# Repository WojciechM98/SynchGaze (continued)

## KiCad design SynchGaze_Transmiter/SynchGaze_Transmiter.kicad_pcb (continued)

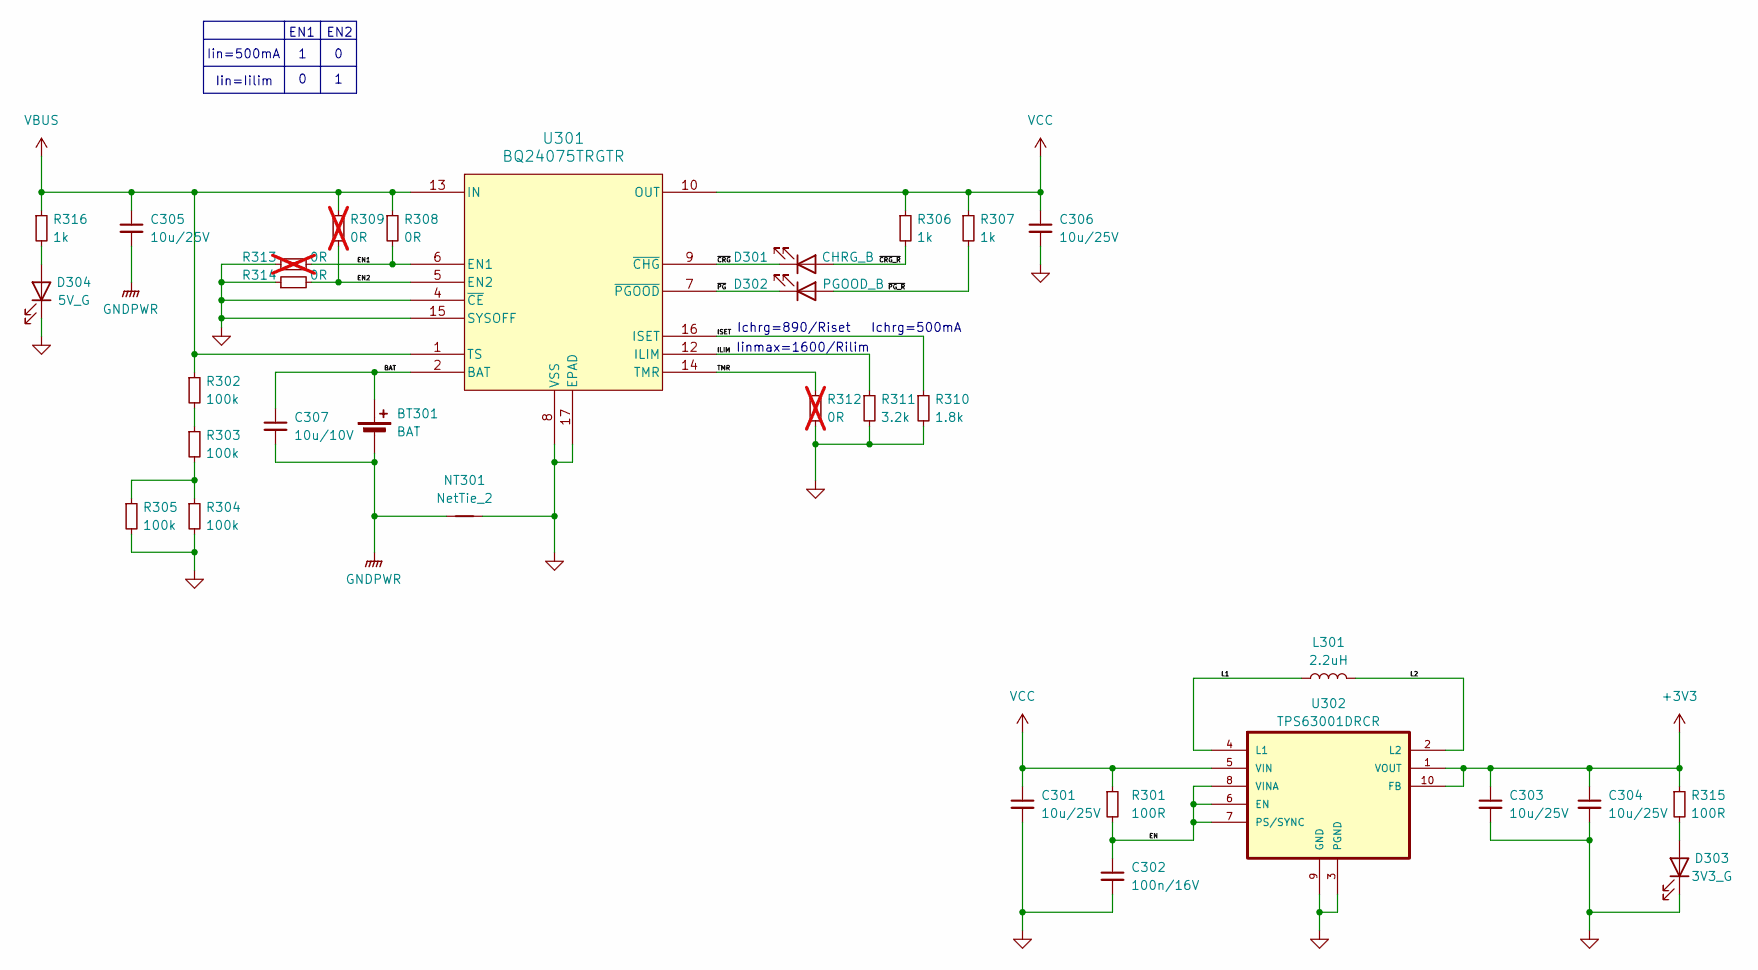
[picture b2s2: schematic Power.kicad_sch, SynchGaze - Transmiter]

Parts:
BT301: BAT; SM02B-SRSS-TB_LF__SN_; Manufacturer Part Number ACCU-LP542439/CL
C301, C303, C304, C305, C306: 10u/25V; C_1206_3216Metric; Manufacturer Part Number CL31B106KAHNFNE
C302: 100n/16V; C_0402_1005Metric; Manufacturer Part Number CL05B104JO5NNNC
C307: 10u/10V; C_0402_1005Metric; Manufacturer Part Number GRM155R61A106ME11J
D301: CHRG_B; LED_0603_1608Metric; Manufacturer Part Number 150060BS55040
D302: PGOOD_B; LED_0603_1608Metric; Manufacturer Part Number 150060BS55040
D303: 3V3_G; LED_0603_1608Metric; Manufacturer Part Number 150060GS55040
D304: 5V_G; LED_0603_1608Metric; Manufacturer Part Number 150060GS55040
L301: 2.2uH; L_Abracon_ASPI-3012S; Manufacturer Part Number NRH3012T2R2MNV
NT301: NetTie_2; NetTie-2_SMD_0.4mm
R301, R315: 100R; R_0402_1005Metric; Manufacturer Part Number RC0402JR-07100RP
R302, R303, R304, R305: 100k; R_0402_1005Metric; Manufacturer Part Number WR04X104 JTL
R306, R307, R316: 1k; R_0402_1005Metric; Manufacturer Part Number RT0402FRE071KL
R308, R314: 0R; R_0402_1005Metric; Manufacturer Part Number RC0402JR-070RP
R309, R312, R313: 0R; R_0402_1005Metric; Manufacturer Part Number RC0402JR-070RP; not fitted
R310: 1.8k; R_0402_1005Metric; Manufacturer Part Number RT0402FRE071K8L
R311: 3.2k; R_0402_1005Metric; Manufacturer Part Number RT0402DRE073K2L
U301: BQ24075TRGTR; Manufacturer Part Number BQ24075TRGTR
U302: TPS63001DRCR; VREG_V62_16624-01YE_TPS63001DRCR; Manufacturer Part Number TPS63001DRCR

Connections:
+3V3: C303.1, C304.1, R315.1, U302.1 (VOUT), U302.10 (FB); also elsewhere on the board
/Power/BAT: BT301.1 (+), C307.1, U301.2 (BAT), U301.3 (BAT)
/Power/EN: C302.1, R301.2, U302.6 (EN), U302.7 (PS/SYNC), U302.8 (VINA)
/Power/EN1: R308.2, R313.2, U301.6 (EN1)
/Power/EN2: R309.2, R314.2, U301.5 (EN2)
/Power/ILIM: R311.1, U301.12 (ILIM)
/Power/ISET: R310.1, U301.16 (ISET)
/Power/L1: L301.1, U302.4 (L1)
/Power/L2: L301.2, U302.2 (L2)
/Power/TMR: R312.1, U301.14 (TMR)
/Power/~CRG_R: D301.2 (A), R306.2
/Power/~CRG: D301.1 (K), U301.9 (~CHG)
/Power/~PG_R: D302.2 (A), R307.2
/Power/~PG: D302.1 (K), U301.7 (~PGOOD)
GND: C301.2, C302.2, C303.2, C304.2, C306.2, D303.1 (K), D304.1 (K), NT301.2, R304.2, R305.2, R310.2, R311.2, R312.2, R313.1, R314.1, U301.4 (~CE), U301.8 (VSS), U301.15 (SYSOFF), U301.17 (EPAD), U302.3 (PGND), U302.9 (GND), U302.11 (POWER_PAD); also elsewhere on the board
GNDPWR: BT301.2 (-), C305.2, C307.2, NT301.1
unnamed: D303.2 (A), R315.2
unnamed: D304.2 (A), R316.2
unnamed: R302.2, R303.1
unnamed: R303.2, R304.1, R305.1
VBUS: C305.1, R302.1, R308.1, R309.1, R316.1, U301.1 (TS), U301.13 (IN); also elsewhere on the board
VCC: C301.1, C306.1, R301.1, R306.1, R307.1, U301.10 (OUT), U301.11 (OUT), U302.5 (VIN)

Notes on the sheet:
Iin=500mA
EN1
EN2
Iin=Iilim
Iinmax=1600/Rilim
Ichrg=500mA
Ichrg=890/Riset

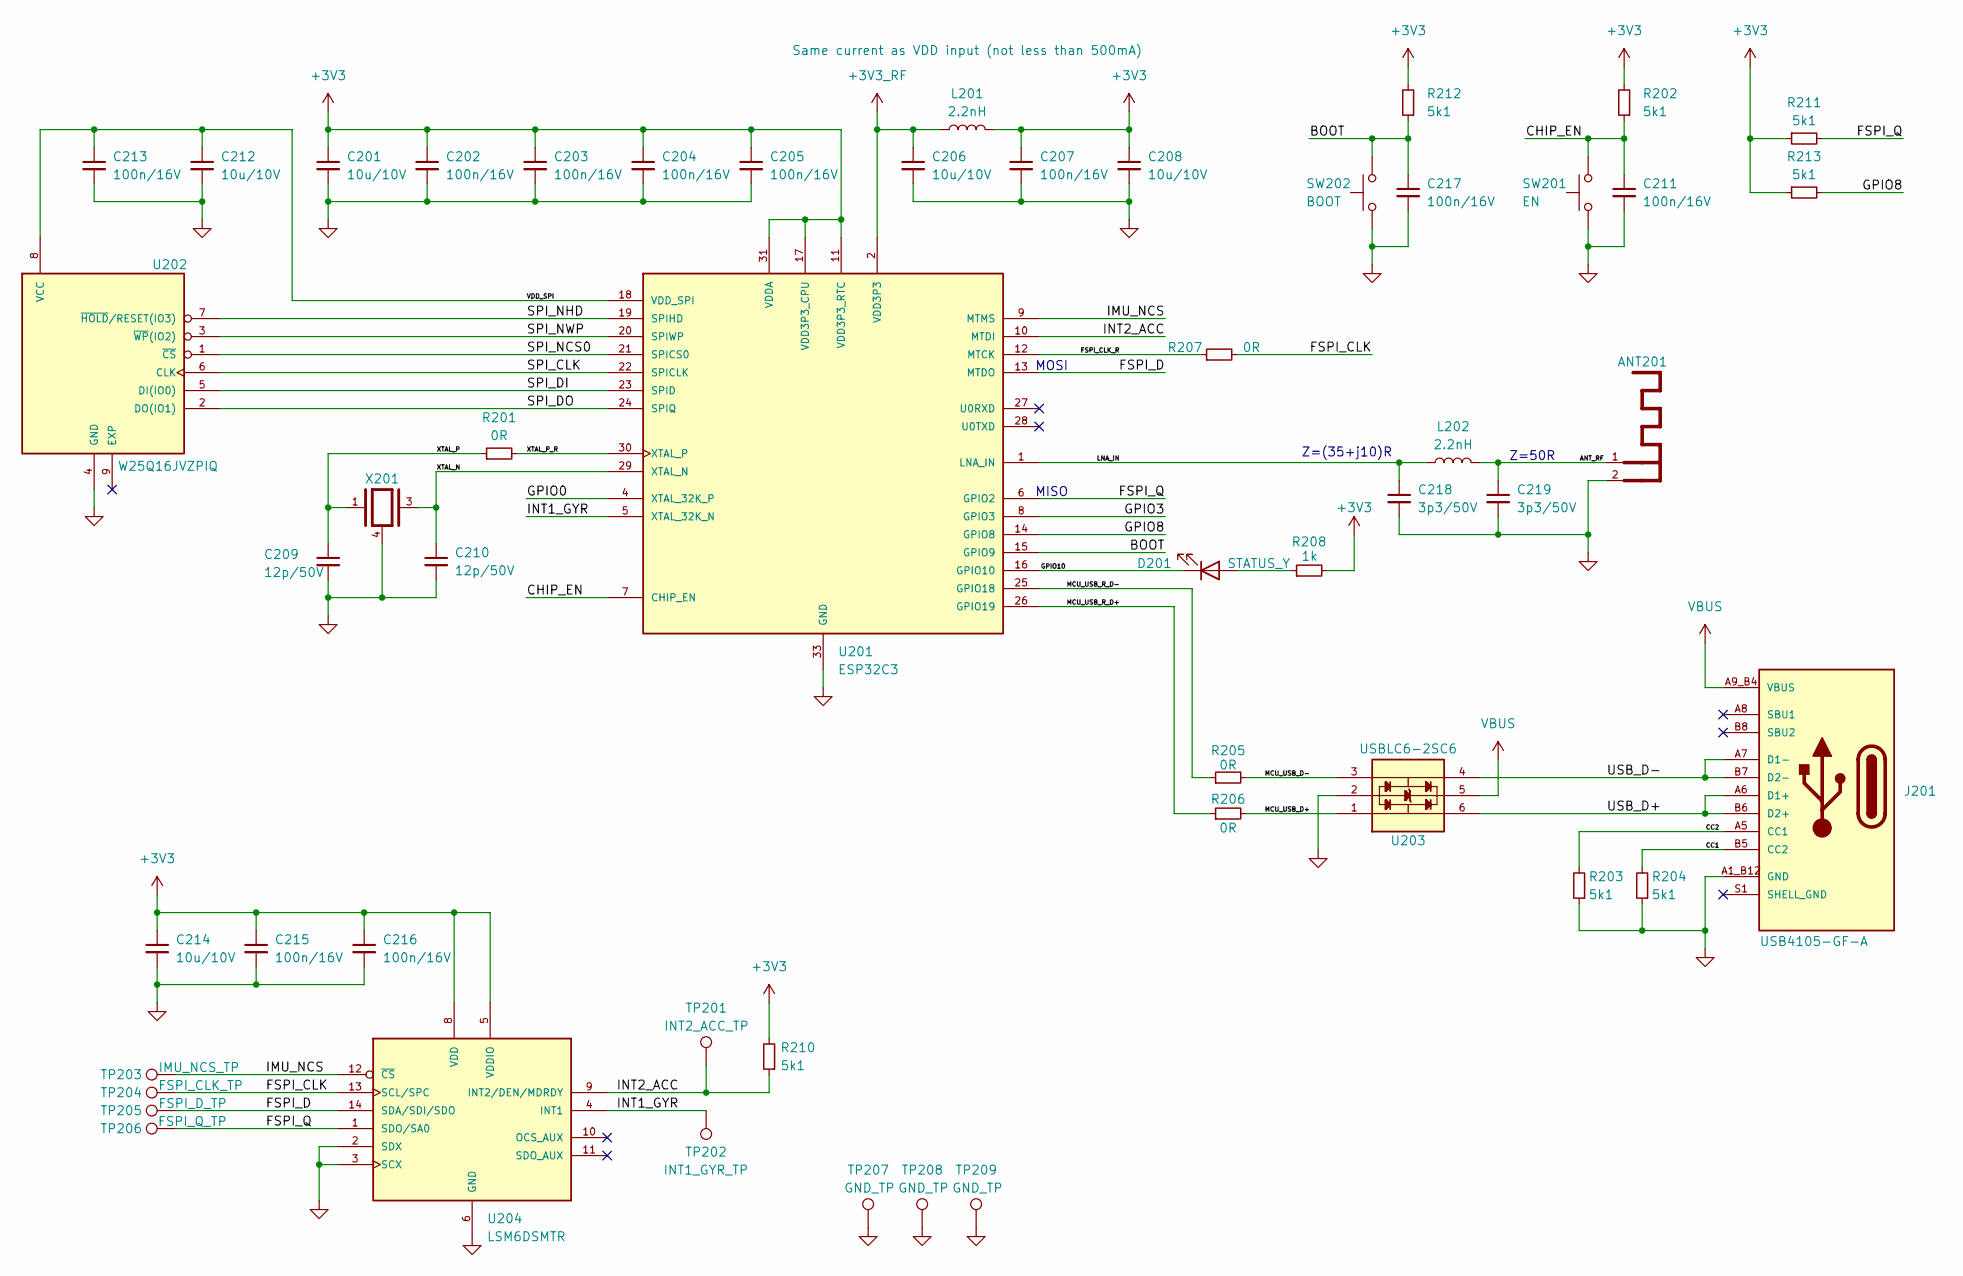
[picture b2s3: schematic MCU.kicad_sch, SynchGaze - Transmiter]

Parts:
ANT201: Ant_2_4ghz_50ohm
C201, C206, C208, C212, C214: 10u/10V; C_0402_1005Metric; Manufacturer Part Number GRM155R61A106ME11J
C202, C203, C204, C205, C207, C211, C213, C215, C216, C217: 100n/16V; C_0402_1005Metric; Manufacturer Part Number CL05B104JO5NNNC
C209, C210: 12p/50V; C_0402_1005Metric; Manufacturer Part Number GRM1555C1H120JA01D
C218, C219: 3p3/50V; C_0402_1005Metric; Manufacturer Part Number 0402N3R3D500CT
D201: STATUS_Y; LED_0603_1608Metric; Manufacturer Part Number 150060YS55040
J201: USB4105-GF-A; GCT_USB4105-GF-A; PARTREV 3
L201, L202: 2.2nH; L_0402_1005Metric; Manufacturer Part Number LQG15HN2N2S02D
R201, R205, R206, R207: 0R; R_0402_1005Metric; Manufacturer Part Number RC0402JR-070RP
R202, R203, R204, R210, R211, R212, R213: 5k1; R_0402_1005Metric; Manufacturer Part Number RT0402FRE075K1L
R208: 1k; R_0402_1005Metric; Manufacturer Part Number RT0402FRE071KL
SW201: EN; SW4_PTS815 SJM 250 SMTR LFS_CNK; Manufacturer Part Number RKB2SJM250SMTR LFS
SW202: BOOT; SW4_PTS815 SJM 250 SMTR LFS_CNK; Manufacturer Part Number RKB2SJM250SMTR LFS
TP201: INT2_ACC_TP; test_point_SMD_0.5mm
TP202: INT1_GYR_TP; test_point_SMD_0.5mm
TP203: IMU_NCS_TP; test_point_SMD_0.5mm
TP204: FSPI_CLK_TP; test_point_SMD_0.5mm
TP205: FSPI_D_TP; test_point_SMD_0.5mm
TP206: FSPI_Q_TP; test_point_SMD_0.5mm
TP207, TP208, TP209: GND_TP; test_point_THT 0.7mm
U201: ESP32C3; QFN32_5X5MM_ESP32C3; Manufacturer Part Number ESP32-C3
U202: W25Q16JVZPIQ; SON127P500X600X80-9N; Manufacturer Part Number W25Q16JVZPIQ
U203: USBLC6-2SC6; SOT95P280X145-6N; Manufacturer Part Number USBLC6-2SC6
U204: LSM6DSMTR; PQFN50P300X250X86-14N_LSM6DSMTR; PARTREV Rev 7
X201: XRCGB40M000F4M02R0; OSC_XRCGB40M000F4M02R0; PARTREV N/A

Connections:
+3V3: C201.1, C202.1, C203.1, C204.1, C205.1, C207.1, C208.1, C214.1, C215.1, C216.1, L201.2, R202.2, R208.2, R210.2, R211.1, R212.2, R213.1, U201.11 (VDD3P3_RTC), U201.17 (VDD3P3_CPU), U201.31 (VDDA), U201.32 (VDDA), U204.5 (VDDIO), U204.8 (VDD); also elsewhere on the board
+3V3_RF: C206.1, L201.1, U201.2 (VDD3P3), U201.3 (VDD3P3)
/MCU/ANT_RF: ANT201.1, C219.1, L202.2
/MCU/BOOT: C217.1, R212.1, SW202.2, U201.15 (GPIO9)
/MCU/CC1: J201.B5 (CC2), R204.2
/MCU/CC2: J201.A5 (CC1), R203.2
/MCU/CHIP_EN: C211.1, R202.1, SW201.2, U201.7 (CHIP_EN)
/MCU/FSPI_CLK: R207.2, TP204.1, U204.13 (SCL/SPC)
/MCU/FSPI_CLK_R: R207.1, U201.12 (MTCK)
/MCU/FSPI_D: TP205.1, U201.13 (MTDO), U204.14 (SDA/SDI/SDO)
/MCU/FSPI_Q: R211.2, TP206.1, U201.6 (GPIO2), U204.1 (SDO/SA0)
/MCU/GPIO0: U201.4 (XTAL_32K_P)
/MCU/GPIO3: U201.8 (GPIO3)
/MCU/GPIO8: R213.2, U201.14 (GPIO8)
/MCU/GPIO10: D201.1 (K), U201.16 (GPIO10)
/MCU/IMU_NCS: TP203.1, U201.9 (MTMS), U204.12 (~CS)
/MCU/INT1_GYR: TP202.1, U201.5 (XTAL_32K_N), U204.4 (INT1)
/MCU/INT2_ACC: R210.1, TP201.1, U201.10 (MTDI), U204.9 (INT2/DEN/MDRDY)
/MCU/LNA_IN: C218.1, L202.1, U201.1 (LNA_IN)
/MCU/MCU_USB_D+: R206.2, U203.1
/MCU/MCU_USB_D-: R205.2, U203.3
/MCU/MCU_USB_R_D+: R206.1, U201.26 (GPIO19)
/MCU/MCU_USB_R_D-: R205.1, U201.25 (GPIO18)
/MCU/SPI_CLK: U201.22 (SPICLK), U202.6 (CLK)
/MCU/SPI_DI: U201.23 (SPID), U202.5 (DI(IO0))
/MCU/SPI_DO: U201.24 (SPIQ), U202.2 (DO(IO1))
/MCU/SPI_NCS0: U201.21 (SPICS0), U202.1 (~CS)
/MCU/SPI_NHD: U201.19 (SPIHD), U202.7 (~HOLD/RESET(IO3))
/MCU/SPI_NWP: U201.20 (SPIWP), U202.3 (~WP(IO2))
/MCU/USB_D+: J201.A6 (D1+), J201.B6 (D2+), U203.6
/MCU/USB_D-: J201.A7 (D1-), J201.B7 (D2-), U203.4
/MCU/VDD_SPI: C212.1, C213.1, U201.18 (VDD_SPI), U202.8 (VCC)
/MCU/XTAL_N: C210.1, U201.29 (XTAL_N), X201.3
/MCU/XTAL_P: C209.1, R201.1, X201.1
/MCU/XTAL_P_R: R201.2, U201.30 (XTAL_P)
GND: ANT201.2, C201.2, C202.2, C203.2, C204.2, C205.2, C206.2, C207.2, C208.2, C209.2, C210.2, C211.2, C212.2, C213.2, C214.2, C215.2, C216.2, C217.2, C218.2, C219.2, J201.A1_B12 (GND), J201.A12_B1 (GND), R203.1, R204.1, SW201.1, SW202.1, TP207.1, TP208.1, TP209.1, U201.33 (GND), U202.4 (GND), U203.2, U204.2 (SDX), U204.3 (SCX), U204.6 (GND), U204.7 (GND), X201.2, X201.4; also elsewhere on the board
unnamed: D201.2 (A), R208.1
VBUS: J201.A4_B9 (VBUS), J201.A9_B4 (VBUS), U203.5; also elsewhere on the board

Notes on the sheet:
Z=50R
Z=(35+j10)R
MOSI
MISO

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
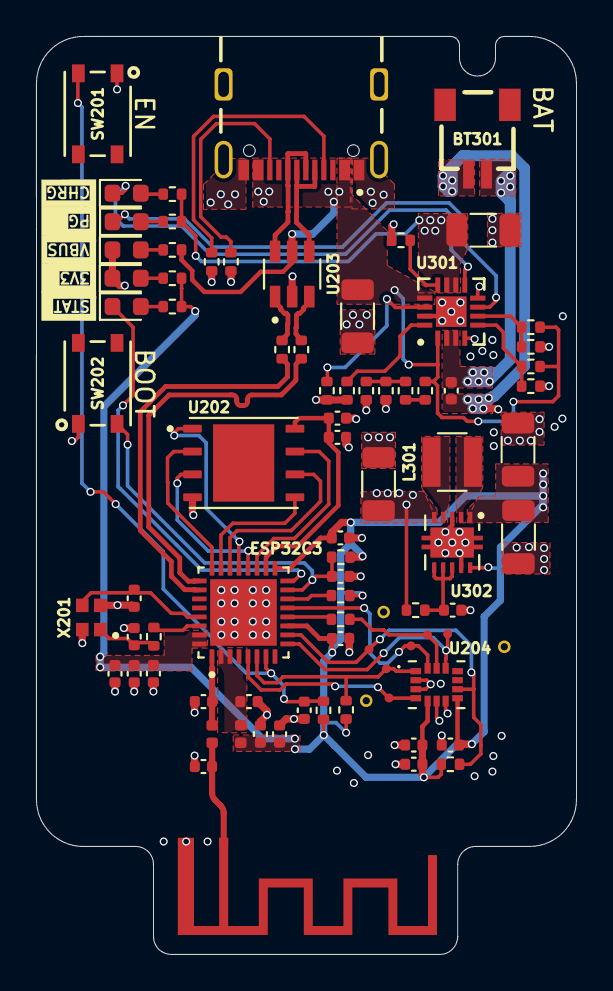
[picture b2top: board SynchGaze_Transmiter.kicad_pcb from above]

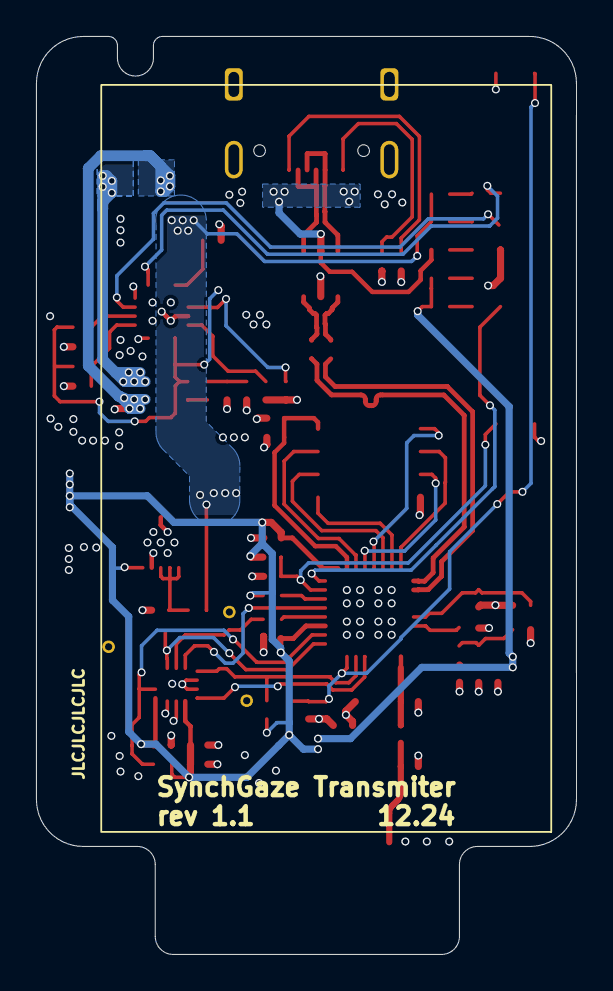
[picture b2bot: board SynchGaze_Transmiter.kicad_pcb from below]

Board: 4 copper layers, 30.0 x 51.0 mm, 85 parts (2 on the bottom side), 55 nets.

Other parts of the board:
ACCU-LP542439/CL: LP542439

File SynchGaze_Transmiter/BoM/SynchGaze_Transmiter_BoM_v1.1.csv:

"Qty","Reference","Value","Footprint","Manufacturer","Manufacturer Part Number","Mouser","TME"
"1","J201","USB4105-GF-A","USB4105-GF-A:GCT_USB4105-GF-A","","","https://www.mouser.pl/ProductDetail/GCT/USB4105-GF-A-120?qs=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",""
"1","TP201","INT2_ACC_TP","TEST_POINT:test_point_SMD_0.5mm","","","",""
"1","TP202","INT1_GYR_TP","TEST_POINT:test_point_SMD_0.5mm","","","",""
"1","TP203","IMU_NCS_TP","TEST_POINT:test_point_SMD_0.5mm","","","",""
"1","TP204","FSPI_CLK_TP","TEST_POINT:test_point_SMD_0.5mm","","","",""
"1","TP205","FSPI_D_TP","TEST_POINT:test_point_SMD_0.5mm","","","",""
"1","TP206","FSPI_Q_TP","TEST_POINT:test_point_SMD_0.5mm","","","",""
"3","TP207,TP208,TP209","GND_TP","TEST_POINT:test_point_THT 0.7mm","","","",""
"1","SW201","EN","RKB2SJM250SMTR_LFS:SW4_PTS815 SJM 250 SMTR LFS_CNK","C&K"," RKB2SJM250SMTR LFS","https://www.mouser.pl/ProductDetail/CK/RKB2SJM250SMTR-LFS?qs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",""
"1","SW202","BOOT","RKB2SJM250SMTR_LFS:SW4_PTS815 SJM 250 SMTR LFS_CNK","C&K"," RKB2SJM250SMTR LFS","https://www.mouser.pl/ProductDetail/CK/RKB2SJM250SMTR-LFS?qs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",""
"1","X201","XRCGB40M000F4M02R0","XRCGB40M000F4M02R0:OSC_XRCGB40M000F4M02R0","Murata Electronics"," XRCGB40M000F4M02R0","https://www.mouser.pl/ProductDetail/Murata-Electronics/XRCGB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",""
"2","C218,C219","3p3/50V","Capacitor_SMD:C_0402_1005Metric","Walsin","0402N3R3D500CT","https://www.mouser.pl/ProductDetail/Walsin/0402N3R3D500CT?qs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",""
"1","D301","CHRG_B","LED_SMD:LED_0603_1608Metric","Wurth Elektronik","150060BS55040","https://www.mouser.pl/ProductDetail/Wurth-Elektronik/150060B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",""
"1","D302","PGOOD_B","LED_SMD:LED_0603_1608Metric","Wurth Elektronik","150060BS55040","https://www.mouser.pl/ProductDetail/Wurth-Elektronik/150060B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",""
"1","D303","3V3_G","LED_SMD:LED_0603_1608Metric","Wurth Elektronik","150060GS55040","https://www.mouser.pl/ProductDetail/Wurth-Elektronik/150060G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",""
"1","D304","5V_G","LED_SMD:LED_0603_1608Metric","Wurth Elektronik","150060GS55040","https://www.mouser.pl/ProductDetail/Wurth-Elektronik/150060G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",""
"1","D201","STATUS_Y","LED_SMD:LED_0603_1608Metric","Wurth Elektronik","150060YS55040","https://www.mouser.pl/ProductDetail/Wurth-Elektronik/150060Y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",""
"1","BT301","BAT","SM02B-SRSS-TB_LF__SN_:SM02B-SRSS-TB_LF__SN_","CELLEVIA BATTERIES","ACCU-LP542439/CL","","https://www.tme.eu/pl/details/accu-lp542439_cl/akumulatory/c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"
"1","U301","BQ24075TRGTR","BQ24075TRGTR:BQ24075TRGTR","Texas Instruments","BQ24075TRGTR","https://www.mouser.pl/ProductDetail/Texas-Instruments/BQ2407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",""
"11","C202,C203,C204,C205,C207,C211,C213,C215,C216,C217,C302","100n/16V","Capacitor_SMD:C_0402_1005Metric","Samsung Electro-Mechanics","CL05B104JO5NNNC","https://www.mouser.pl/ProductDetail/Samsung-Electro-Mechanic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",""
"5","C301,C303,C304,C305,C306","10u/25V","Capacitor_SMD:C_1206_3216Metric","Samsung Electro-Mechanics","CL31B106KAHNFNE","https://www.mouser.pl/ProductDetail/Samsung-Electro-Mechanic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",""
"1","U201","ESP32C3","ESP32C3:QFN32_5X5MM_ESP32C3","Espressif Systems","ESP32-C3","https://www.mouser.pl/ProductDetail/Espressif-Systems/ESP32-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",""
"2","C209,C210","12p/50V","Capacitor_SMD:C_0402_1005Metric","Murata Electronics","GRM1555C1H120JA01D","https://www.mouser.pl/ProductDetail/Murata-Electronics/GRM15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",""
"6","C201,C206,C208,C212,C214,C307","10u/10V","Capacitor_SMD:C_0402_1005Metric","Murata Electronics","GRM155R61A106ME11J","https://www.mouser.pl/ProductDetail/Murata-Electronics/GRM15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",""
"2","L201,L202","2.2nH","Inductor_SMD:L_0402_1005Metric","Murata Electronics","LQG15HN2N2S02D","https://www.mouser.pl/ProductDetail/Murata-Electronics/LQG15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",""
"1","U204","LSM6DSMTR","LSM6DSMTR:PQFN50P300X250X86-14N_LSM6DSMTR","STMicroelectronics","LSM6DSMTR","https://www.mouser.pl/ProductDetail/STMicroelectronics/LSM6D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",""
"1","L301","2.2uH","Inductor_SMD:L_Abracon_ASPI-3012S","TAIYO YUDEN","NRH3012T2R2MNV","https://www.mouser.pl/ProductDetail/TAIYO-YUDEN/NRH3012T2R2M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",""
"9","R201,R205,R206,R207,R308,R309,R312,R313,R314","0R","Resistor_SMD:R_0402_1005Metric","YAGEO","RC0402JR-070RP","https://www.mouser.pl/ProductDetail/YAGEO/RC0402JR-070RP?qs=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",""
"2","R301,R315","100R","Resistor_SMD:R_0402_1005Metric","YAGEO","RC0402JR-07100RP","https://www.mouser.pl/ProductDetail/YAGEO/RC0402JR-07100RP?q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",""
"1","R311","3.2k","Resistor_SMD:R_0402_1005Metric","YAGEO","RT0402DRE073K2L","https://www.mouser.pl/ProductDetail/YAGEO/RT0402DRE073K2L?qs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",""
"4","R208,R306,R307,R316","1k","Resistor_SMD:R_0402_1005Metric","YAGEO","RT0402FRE071KL","https://www.mouser.pl/ProductDetail/YAGEO/RT0402FRE071KL?qs=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",""
"1","R310","1.8k","Resistor_SMD:R_0402_1005Metric","YAGEO","RT0402FRE071K8L","https://www.mouser.pl/ProductDetail/YAGEO/RT0402FRE071K8L?qs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",""
"7","R202,R203,R204,R210,R211,R212,R213","5k1","Resistor_SMD:R_0402_1005Metric","YAGEO","RT0402FRE075K1L","https://www.mouser.pl/ProductDetail/YAGEO/RT0402FRE075K1L?qs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",""
"1","U302","TPS63001DRCR","TPS63001DRCR:VREG_V62_16624-01YE_TPS63001DRCR","Texas Instruments","TPS63001DRCR","https://www.mouser.pl/ProductDetail/Texas-Instruments/TPS630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",""
"1","U203","USBLC6-2SC6","USBLC6-2SC6:SOT95P280X145-6N","STMicroelectronics","USBLC6-2SC6","https://www.mouser.pl/ProductDetail/STMicroelectronics/USBLC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",""
"1","U202","W25Q16JVZPIQ","W25Q16JVZPIQ:SON127P500X600X80-9N","Winbond","W25Q16JVZPIQ","https://www.mouser.pl/ProductDetail/Winbond/W25Q16JVZPIQ?qs=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",""
"4","R302,R303,R304,R305","100k","Resistor_SMD:R_0402_1005Metric","Walsin","WR04X104 JTL","https://www.mouser.pl/ProductDetail/Walsin/WR04X104-JTL?qs=1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",""

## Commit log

2024-09-21 First develop version rev 1.0
2024-09-22 Readme file update
2025-01-06 rev 1.1
2025-01-06 Small changes
2025-01-06 Changed screenshots names to match PCB revision
2025-01-06 Updated README with new screenshots
